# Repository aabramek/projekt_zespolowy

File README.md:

# projekt_zespolowy
Projekt zespołowy na studiach

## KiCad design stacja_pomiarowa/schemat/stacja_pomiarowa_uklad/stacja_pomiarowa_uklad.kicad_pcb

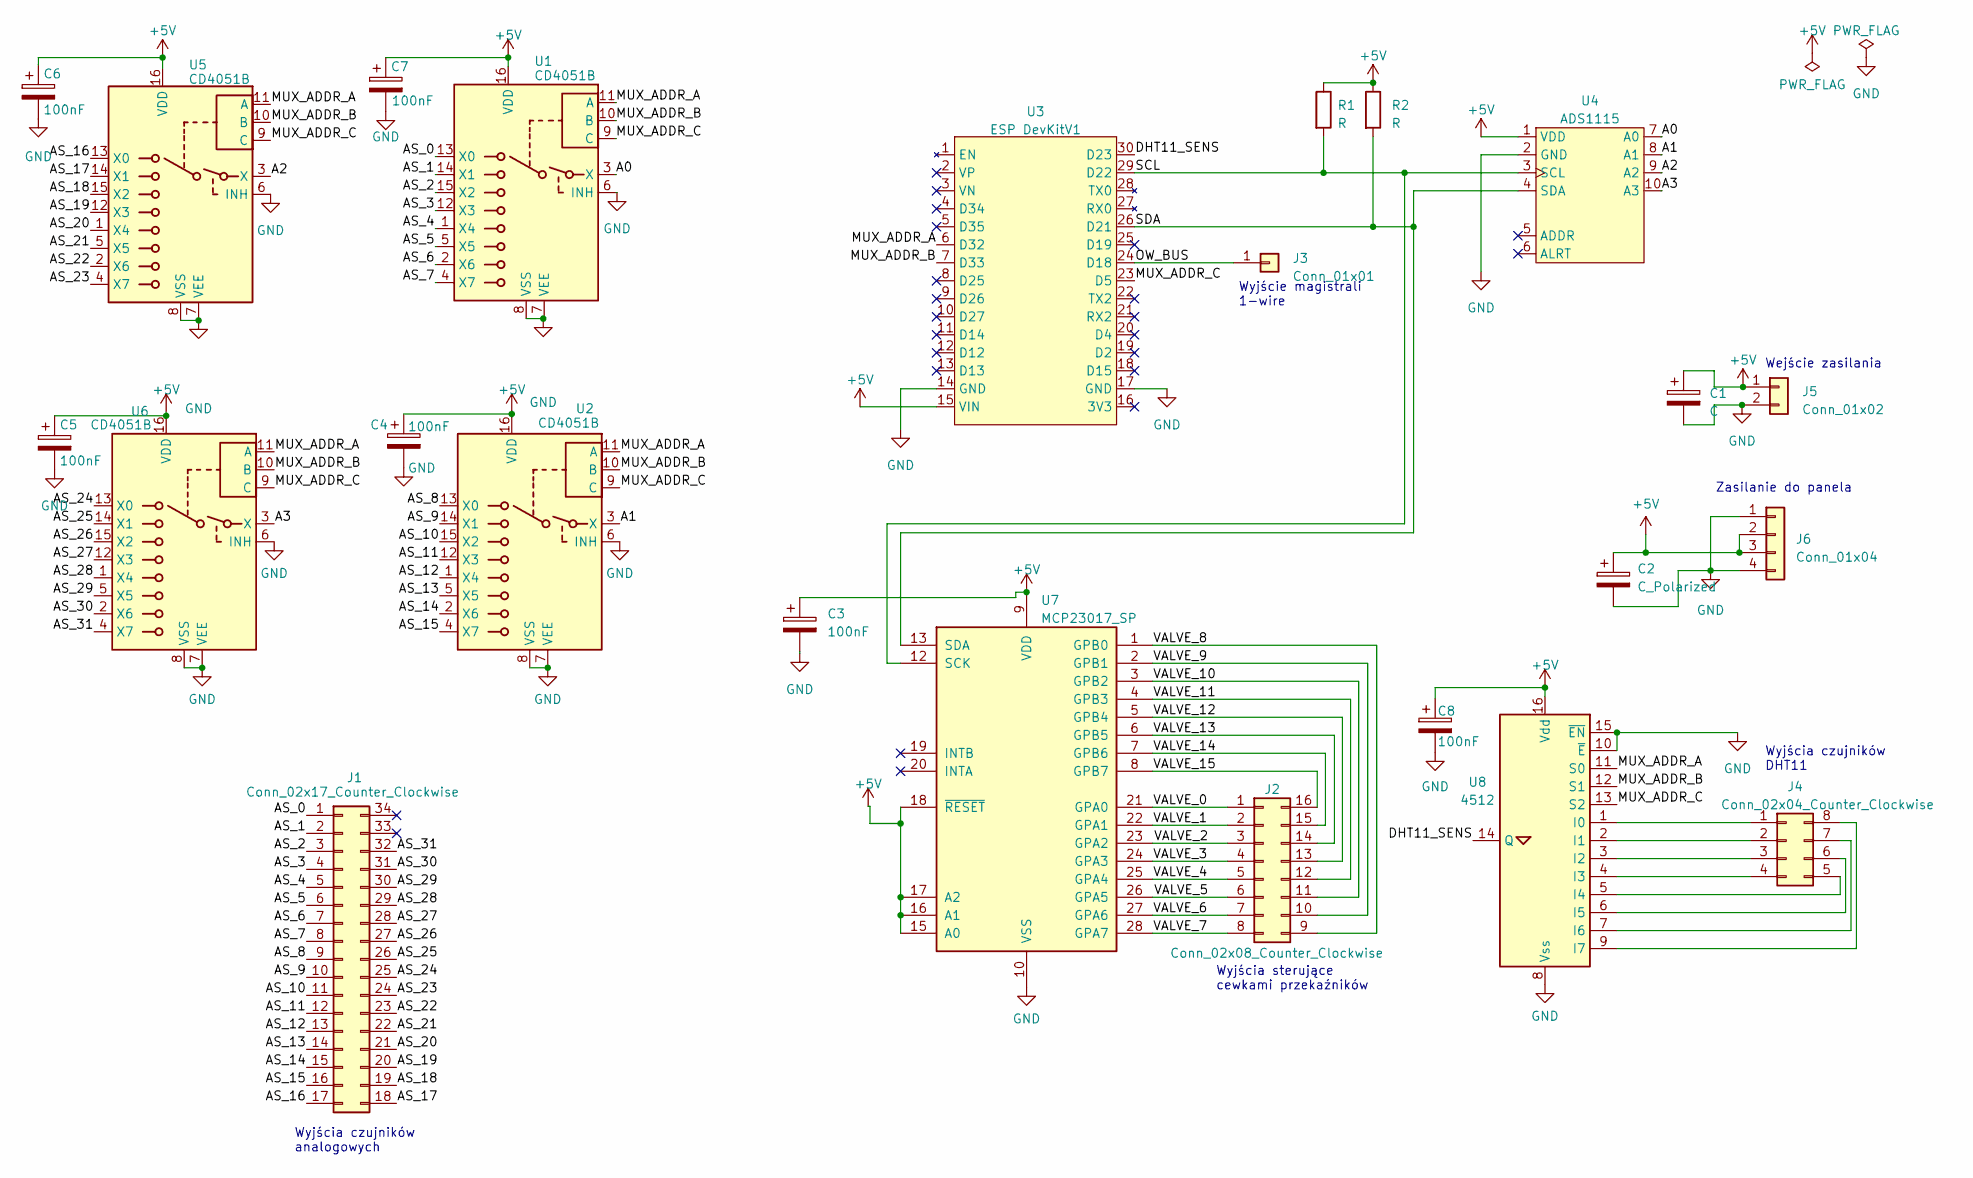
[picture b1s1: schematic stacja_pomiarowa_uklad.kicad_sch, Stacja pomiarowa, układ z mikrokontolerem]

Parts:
C1: C; CP_Radial_D5.0mm_P2.50mm
C2: C_Polarized; CP_Radial_D5.0mm_P2.50mm
C3, C4, C5, C6, C7, C8: 100nF; C_Disc_D4.3mm_W1.9mm_P5.00mm
J1: Conn_02x17_Counter_Clockwise; IDC-Header_2x17_P2.54mm_Vertical
J2: Conn_02x08_Counter_Clockwise; IDC-Header_2x08_P2.54mm_Vertical
J3: Conn_01x01; PinHeader_1x01_P2.54mm_Vertical
J4: Conn_02x04_Counter_Clockwise; IDC-Header_2x04_P2.54mm_Vertical
J5: Conn_01x02; ARK_x2_P2.54
J6: Conn_01x04; SolderWire-2sqmm_1x04_P7.8mm_D2mm_OD3.9mm
R1, R2: R; R_Axial_DIN0207_L6.3mm_D2.5mm_P7.62mm_Horizontal
U1, U2, U5, U6: CD4051B; DIP-16_W7.62mm_Socket
U3: ESP DevKitV1
U4: ADS1115; PinHeader_1x10_P2.54mm_Vertical
U7: MCP23017_SP; DIP-28_W7.62mm
U8: 4512; DIP-16_W7.62mm_Socket

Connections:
+5V: C1.1, C2.1, C3.1, C4.1, C5.1, C6.1, C7.1, C8.1, J5.1, J6.2, J6.3, R1.1, R2.1, U1.16 (VDD), U2.16 (VDD), U3.15 (VIN), U4.1 (VDD), U5.16 (VDD), U6.16 (VDD), U7.9 (VDD), U7.15 (A0), U7.16 (A1), U7.17 (A2), U7.18 (~RESET), U8.16 (Vdd)
/A0: U1.3 (X), U4.7 (A0)
/A1: U2.3 (X), U4.8 (A1)
/A2: U4.9 (A2), U5.3 (X)
/A3: U4.10 (A3), U6.3 (X)
/AS_0: J1.1, U1.13 (X0)
/AS_1: J1.2, U1.14 (X1)
/AS_2: J1.3, U1.15 (X2)
/AS_3: J1.4, U1.12 (X3)
/AS_4: J1.5, U1.1 (X4)
/AS_5: J1.6, U1.5 (X5)
/AS_6: J1.7, U1.2 (X6)
/AS_7: J1.8, U1.4 (X7)
/AS_8: J1.9, U2.13 (X0)
/AS_9: J1.10, U2.14 (X1)
/AS_10: J1.11, U2.15 (X2)
/AS_11: J1.12, U2.12 (X3)
/AS_12: J1.13, U2.1 (X4)
/AS_13: J1.14, U2.5 (X5)
/AS_14: J1.15, U2.2 (X6)
/AS_15: J1.16, U2.4 (X7)
/AS_16: J1.17, U5.13 (X0)
/AS_17: J1.18, U5.14 (X1)
/AS_18: J1.19, U5.15 (X2)
/AS_19: J1.20, U5.12 (X3)
/AS_20: J1.21, U5.1 (X4)
/AS_21: J1.22, U5.5 (X5)
/AS_22: J1.23, U5.2 (X6)
/AS_23: J1.24, U5.4 (X7)
/AS_24: J1.25, U6.13 (X0)
/AS_25: J1.26, U6.14 (X1)
/AS_26: J1.27, U6.15 (X2)
/AS_27: J1.28, U6.12 (X3)
/AS_28: J1.29, U6.1 (X4)
/AS_29: J1.30, U6.5 (X5)
/AS_30: J1.31, U6.2 (X6)
/AS_31: J1.32, U6.4 (X7)
/DHT11_SENS: U3.30 (D23), U8.14 (Q)
/MUX_ADDR_A: U1.11 (A), U2.11 (A), U3.6 (D32), U5.11 (A), U6.11 (A), U8.11 (S0)
/MUX_ADDR_B: U1.10 (B), U2.10 (B), U3.7 (D33), U5.10 (B), U6.10 (B), U8.12 (S1)
/MUX_ADDR_C: U1.9 (C), U2.9 (C), U3.23 (D5), U5.9 (C), U6.9 (C), U8.13 (S2)
/OW_BUS: J3.1, U3.24 (D18)
/SCL: R1.2, U3.29 (D22), U4.3 (SCL), U7.12 (SCK)
/SDA: R2.2, U3.26 (D21), U4.4 (SDA), U7.13 (SDA)
/VALVE_0: J2.1, U7.21 (GPA0)
/VALVE_1: J2.2, U7.22 (GPA1)
/VALVE_2: J2.3, U7.23 (GPA2)
/VALVE_3: J2.4, U7.24 (GPA3)
/VALVE_4: J2.5, U7.25 (GPA4)
/VALVE_5: J2.6, U7.26 (GPA5)
/VALVE_6: J2.7, U7.27 (GPA6)
/VALVE_7: J2.8, U7.28 (GPA7)
/VALVE_8: J2.9, U7.1 (GPB0)
/VALVE_9: J2.10, U7.2 (GPB1)
/VALVE_10: J2.11, U7.3 (GPB2)
/VALVE_11: J2.12, U7.4 (GPB3)
/VALVE_12: J2.13, U7.5 (GPB4)
/VALVE_13: J2.14, U7.6 (GPB5)
/VALVE_14: J2.15, U7.7 (GPB6)
/VALVE_15: J2.16, U7.8 (GPB7)
GND: C1.2, C2.2, C3.2, C4.2, C5.2, C6.2, C7.2, C8.2, J5.2, J6.1, J6.4, U1.6 (INH), U1.7 (VEE), U1.8 (VSS), U2.6 (INH), U2.7 (VEE), U2.8 (VSS), U3.14 (GND), U3.17 (GND), U4.2 (GND), U5.6 (INH), U5.7 (VEE), U5.8 (VSS), U6.6 (INH), U6.7 (VEE), U6.8 (VSS), U7.10 (VSS), U8.8 (Vss), U8.10 (~E), U8.15 (~EN)
unnamed: J4.1, U8.1 (I0)
unnamed: J4.2, U8.2 (I1)
unnamed: J4.3, U8.3 (I2)
unnamed: J4.4, U8.4 (I3)
unnamed: J4.5, U8.5 (I4)
unnamed: J4.6, U8.6 (I5)
unnamed: J4.7, U8.7 (I6)
unnamed: J4.8, U8.9 (I7)

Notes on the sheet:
Wyjścia sterujące cewkami przekaźników
Wyjścia czujników DHT11
Wyjście magistrali 1-wire
Wejście zasilania
Zasilanie do panela
Wyjścia czujników analogowych

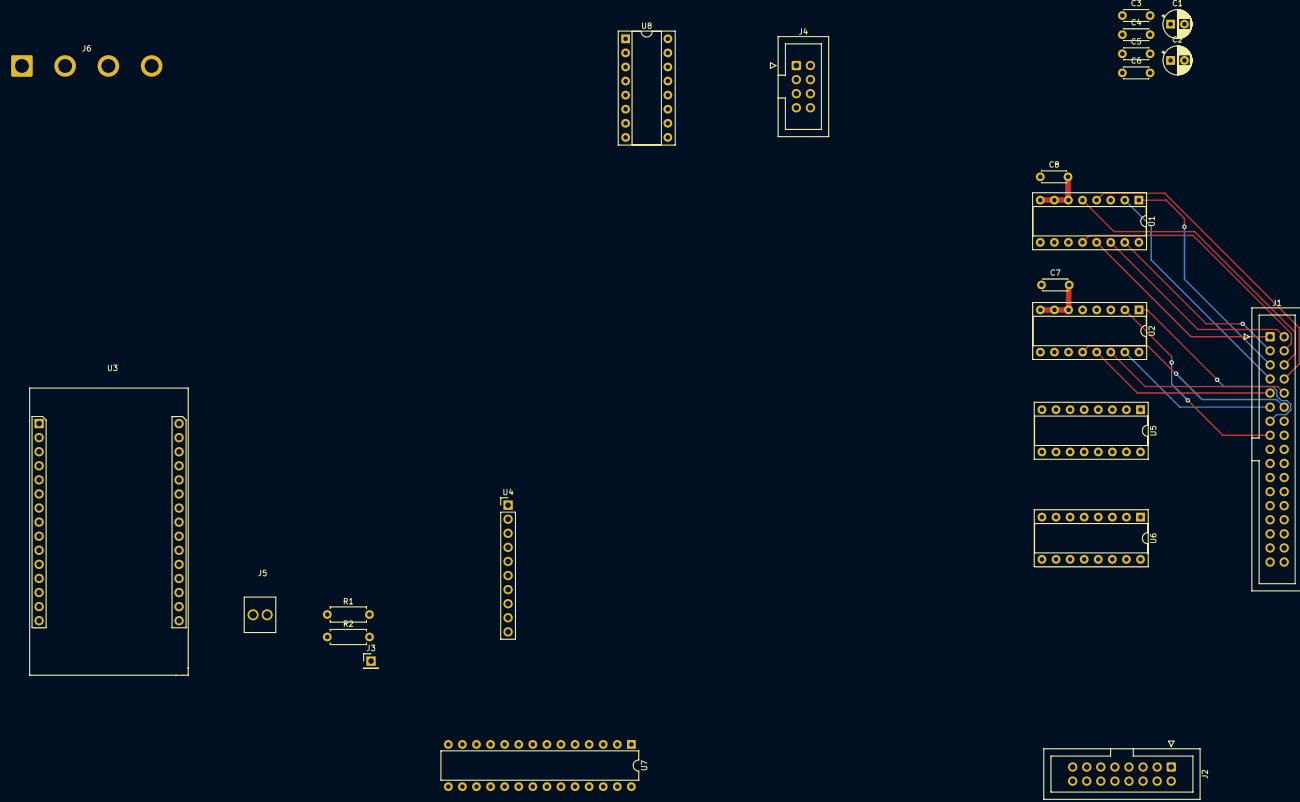
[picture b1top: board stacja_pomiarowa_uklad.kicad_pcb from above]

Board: 2 copper layers, 24 parts (0 on the bottom side), 69 nets.

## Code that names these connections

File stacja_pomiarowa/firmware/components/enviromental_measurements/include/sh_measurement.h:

#ifndef SOIL_HUMIDITY_MEASUREMENT
#define SOIL_HUMIDITY_MEASUREMENT

#define INPUT_LINE_OCCUPIED 1
#define INPUT_LINE_FREE 2

#define MUX_ADDR_A GPIO_NUM_32
#define MUX_ADDR_B GPIO_NUM_33
#define MUX_ADDR_C GPIO_NUM_5

#include "esp_check.h"

extern uint32_t _sh_sensors;

esp_err_t sh_measurement_init(void);

uint32_t sh_measurement_add_sensors(uint32_t sensors);

uint32_t sh_measurement_remove_sensors(uint32_t input_line);

uint32_t sh_measurement_check_sensors(uint32_t input_line);

esp_err_t sh_measure(uint32_t *results);

#endif

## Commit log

2023-03-26 Dodany wstępny opis projektu
    Do zrobienia: przetwarzanie danych, może poprawa wymagań funkcjonalnych
2023-03-28 Poprawiony wstępny opis projektu
    Rozwinięte wymagania funkcjonalne, uzupełniona sekcja "Przetwarzanie danych"
2023-10-20 Powrot do starych smieci
2023-10-20 Porzadki
    Przeniesiono ogrodnik.docx do dokumentacja/
2023-10-25 Poprawa modelu danych, dodane nowe diagramy
2023-10-27 Rejestracja stacji
2023-11-03 Dodano obsluge ukladu ads1115
2023-11-03 Zmiana parametrow na 16-bitowe
2023-11-04 zmiany w sterowniku do mcp23017
2023-11-04 zmiany w sterowniku do ads1115
    struktura opisujaca urzadzenie zawiera numer portu i2c, funkcje zmieniajace konfiguracja zmieniaja zmienna lokalna, nic nie wysylaja do urzadzenia
2023-11-09 Dodana obsluge ukladu dht11
2023-11-12 Dodano osbluge 1wire i sterownik do ds18b20
2023-11-15 Nowy schemat elektroniczny
2023-11-15 Usuniecie komponentu enviromental_measurements
    Byl zupelnie zbedny
2023-11-16 Refaktoryzacja kodu, zmiana struktury Station_t
    Linijka kodu nie przekracza teraz 80 znakow, dane ze struktury Station_t pogrupowane w anonimowe podstruktury, brak zmiennych globalnych, instancja stacji jest tworzona przez funkcje Station_Create
2023-11-26 Dodano schematy wiadomosci
2023-11-26 Nowe schematy wiadomosci
    Schematy dla rejestracji i konfiguracji, pomiary uzupelnione o brakujace pola oraz dodano tam opisy
2023-11-27 Dodano wykonywanie pomiarow
    Oprocz tego troche zrefaktoryzowany kod
2023-11-27 Dodano komponenty odpowiedzialne za pomiary
    Brakowalo ich w poprzednim commicie
2023-11-27 Przywrocenie formy komunikacji taskow pomiarowych do powiadomien
    Grupa zdarzen jest gorsza bo wymaga dodatkowo kolejki / innego bufora danych, zmiana w sdkconfig - taski moga tablica z powiadomieniami taskow ma rozmiar 3
2023-11-27 Poprawa schematu
    Poprzednia numeracja wyjsc analogowych, dodany brakujacy tranzystor Q1, dodane brakujace oporniki podciagajace dla 1-wire i dht11, usuniete oporniki sciagajace dla wyjsc a[0..1] adc - w ten sposob pr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
2023-11-28 Dodano komponent watering
    Zawiera funkcje potrzebne do sterowania podlewaniem, funkcja tasku odpowiedzialnego za podlewanie zostala przeniesiona z komponentu 'station' do komponentu 'watering'
2023-11-28 dodanie serwera BE
2023-11-28 Revert "dodanie serwera BE"
    This reverts commit 05bfc663ee225517501bc6d5a3224ca42a9aac9b.
2023-11-28 dodanie serwera BE - naprawiono
2023-11-28 dodanie serwera BE - dodano brakujące pliki
2023-11-30 Usunieto niepotrzebne pliki z folderu dokumentacja
2023-11-30 added configuration aplication and integration test
2023-11-30 Poprawienie nazwy klucza głównego w tabeli Sensors to tabeli Warnings
2023-12-02 dodano usługę GET /api/station/information/get/{id} do zwracania szczegółowych informacji o stacji
2023-12-03 dodano usługę POST /api/measurements/data/{id} do zwracania danych pomiarowych stacji
2023-12-03 usunięto niepotrzebny folder serwer_be
2023-12-03 Poprawiono schematy wiadomości - dodano wymagania pól
2023-12-03 Dodano wstępną wersję odbioru konfiguracji
    Rozpoznawane jest pole "period", wiadomość która nie przechodzi parsowania json jest odrzucana
2023-12-04 Naprawiono odczyt wartości ujemnych, poprawiono błąd w sterowniku do ads1115 gdzie każdy zapis konfiguracji powodował start konwersji, zwiększono czas oczekiwania na konwersję
    W przyszłości trzeba zastosować przerwanie od ads1115 gdyż vTaskDelay czeka za krótko i czas trzeba ustalać metodą prób i błędów
2023-12-05 dodano testy integracyjne dla metod GET /api/station/get/list, GET /api/station/settings/get/%d oraz dla rejestracji stacji - MosquittoRegisterProcessorImpl
2023-12-06 Dodano obsługę harmonogramu podlewania
2023-12-06 Dodano do fragmentu schematu z przekaźnikami zewnętrzne źródło zasilania AC
2023-12-08 Zmiana multipleksera 4512 na 4051
2023-12-09 Przywrócono oporniki do wejść ads1115, dodano brakujące oporniki do wejść multipleksera od dht11
2023-12-21 Dodanie konsoli do konfiguracji mqtt i wifi, zmiana kofiguracji - nie wszystkie pola są wymagane, zmienane są wartości tylko te które przyszły w wiadomości
2023-12-22 Poprawiona wiadomość z wynikami pomiarów, przy braku czujników cyfrowych występował błąd
2023-12-23 Dodanie tabeli reprezentującej naruszenia ostrzeżeń
2023-12-23 Zmiana złącza zasilania do panela z 4-pinowego na 2-pinowe
2024-01-04 Dodane komendy stationcfg i wateringcfg
2024-01-06 Poprawiono czytelnosc wyswietlanej konfiguracji elektrozaworow
2024-01-06 Dodano ledy informujące czy urządzenie połączyło się z systemem, dodane tytuły podschematów ze złączami
